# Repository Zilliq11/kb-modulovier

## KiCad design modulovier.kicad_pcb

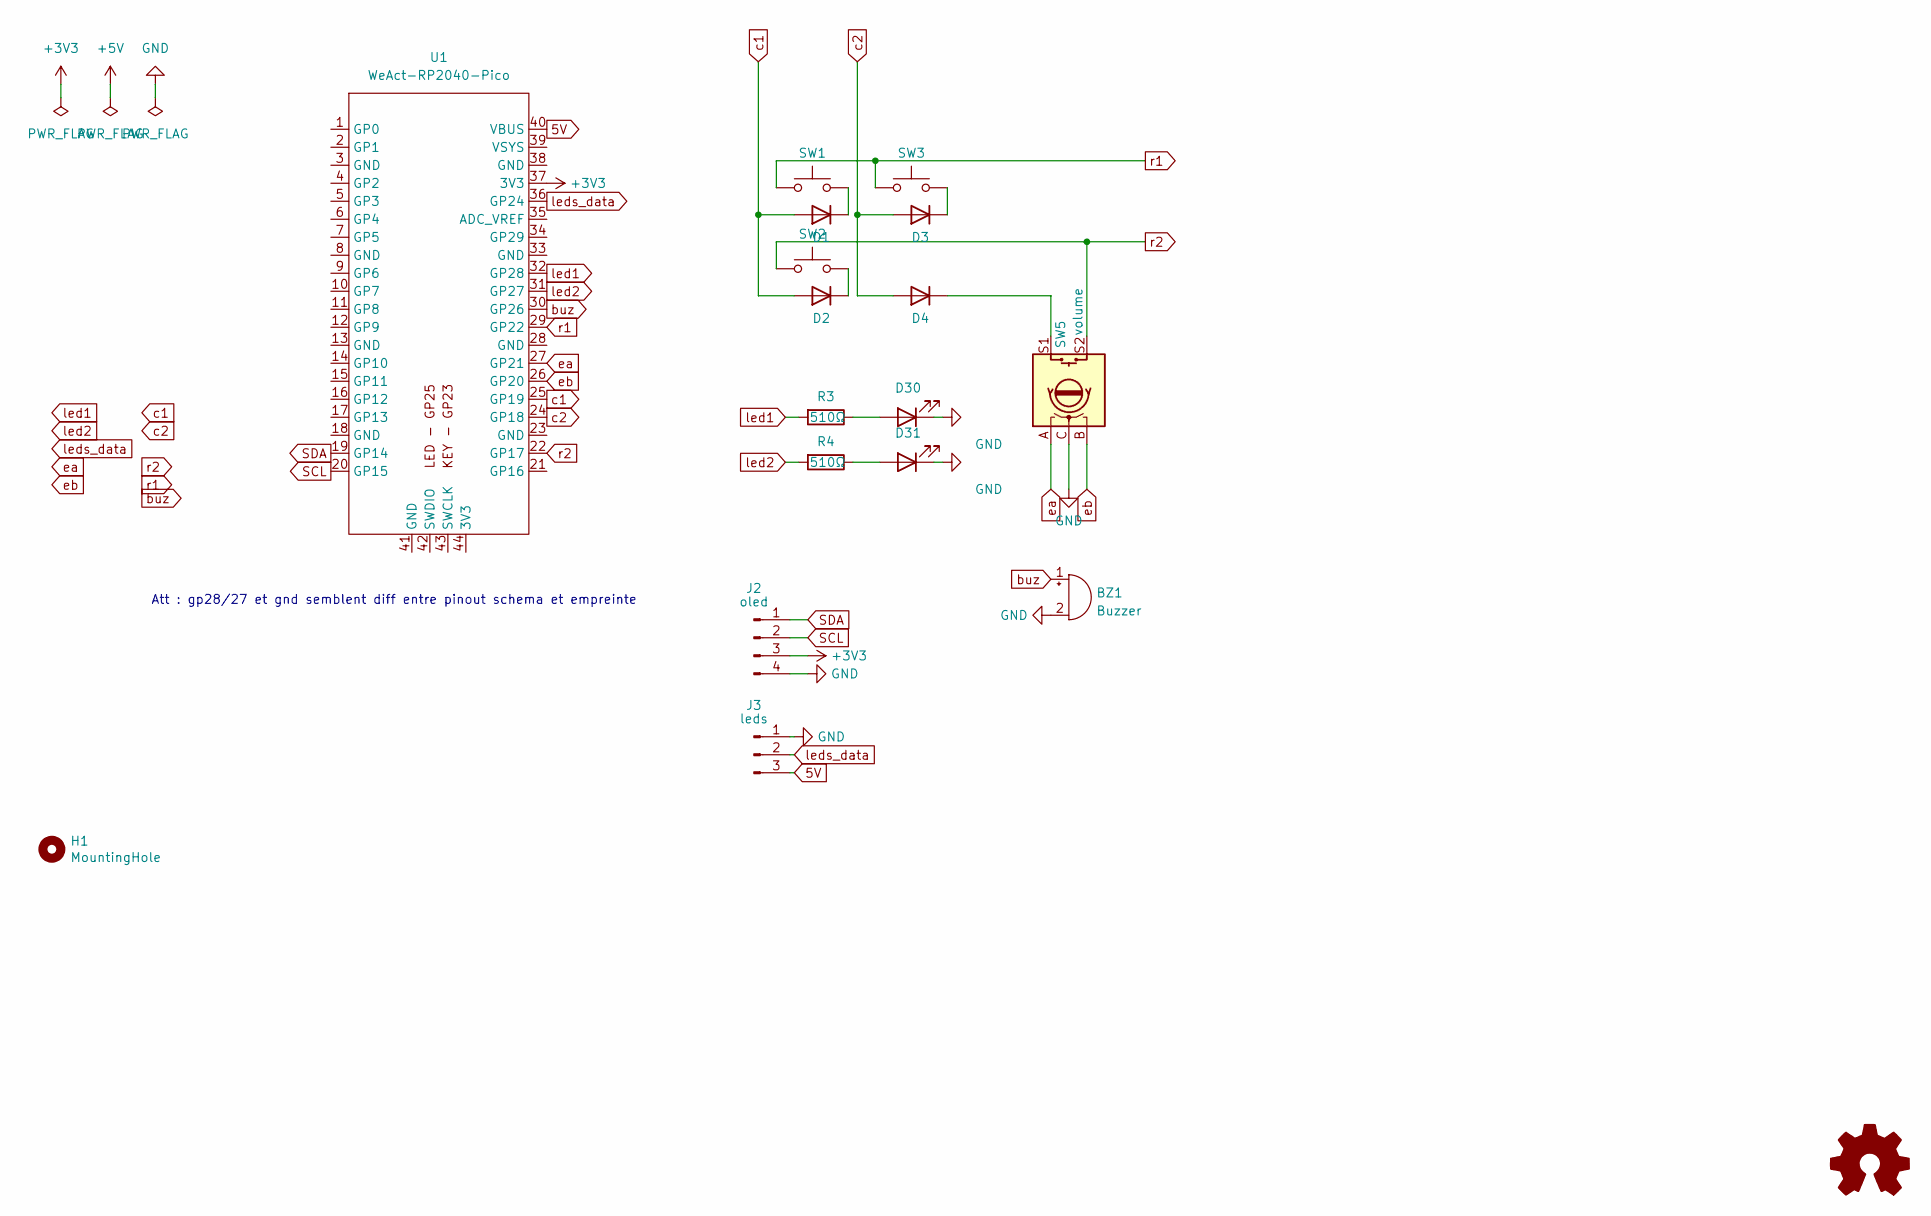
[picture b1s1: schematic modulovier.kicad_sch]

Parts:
BZ1: Buzzer; Buzzer_12x9.5RM7.6
D1, D2, D3, D4: D; D_1206_3216Metric_Pad1.42x1.75mm_HandSolder
D30: LED; LED_D3.0mm_lwr
D31: LED; LED_D3.0mm_rse
H1: MountingHole; LegoHole_12x12u_4875
J2: oled; OLED_128x32
J3: leds; JST_EH_S3B-EH_1x03_P2.50mm_Horizontal
R3, R4: 510Ω; R_1206_3216Metric_Pad1.30x1.75mm_HandSolder
SW1, SW2, SW3: mx; SW_Cherry_MX_1.00u_PCB
SW5: volume; RotaryEncoder_Alps_EC11E_Vertical_H20mm
U1: WeAct-RP2040-Pico

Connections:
5V: J3.3, U1.40 (VBUS)
+3V3: J2.3, U1.37 (3V3)
GND: BZ1.2 (+), D30.1 (K), D31.1 (K), J2.4, J3.1, SW5.C
unnamed: D1.1 (K), SW1.2
unnamed: D2.1 (K), SW2.2
unnamed: D3.1 (K), SW3.2
unnamed: D4.1 (K), SW5.S1
unnamed: D30.2 (A), R3.1
unnamed: D31.2 (A), R4.1
SCL: J2.2, U1.20 (GP15)
SDA: J2.1, U1.19 (GP14)
buz: BZ1.1 (-), U1.30 (GP26)
c1: D1.2 (A), D2.2 (A), U1.25 (GP19)
c2: D3.2 (A), D4.2 (A), U1.24 (GP18)
ea: SW5.A, U1.27 (GP21)
eb: SW5.B, U1.26 (GP20)
led1: R3.2, U1.32 (GP28)
led2: R4.2, U1.31 (GP27)
leds_data: J3.2, U1.36 (GP24)
r1: SW1.1, SW3.1, U1.29 (GP22)
r2: SW2.1, SW5.S2, U1.22 (GP17)

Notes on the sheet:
Att : gp28/27 et gnd semblent diff entre pinout schema et empreinte

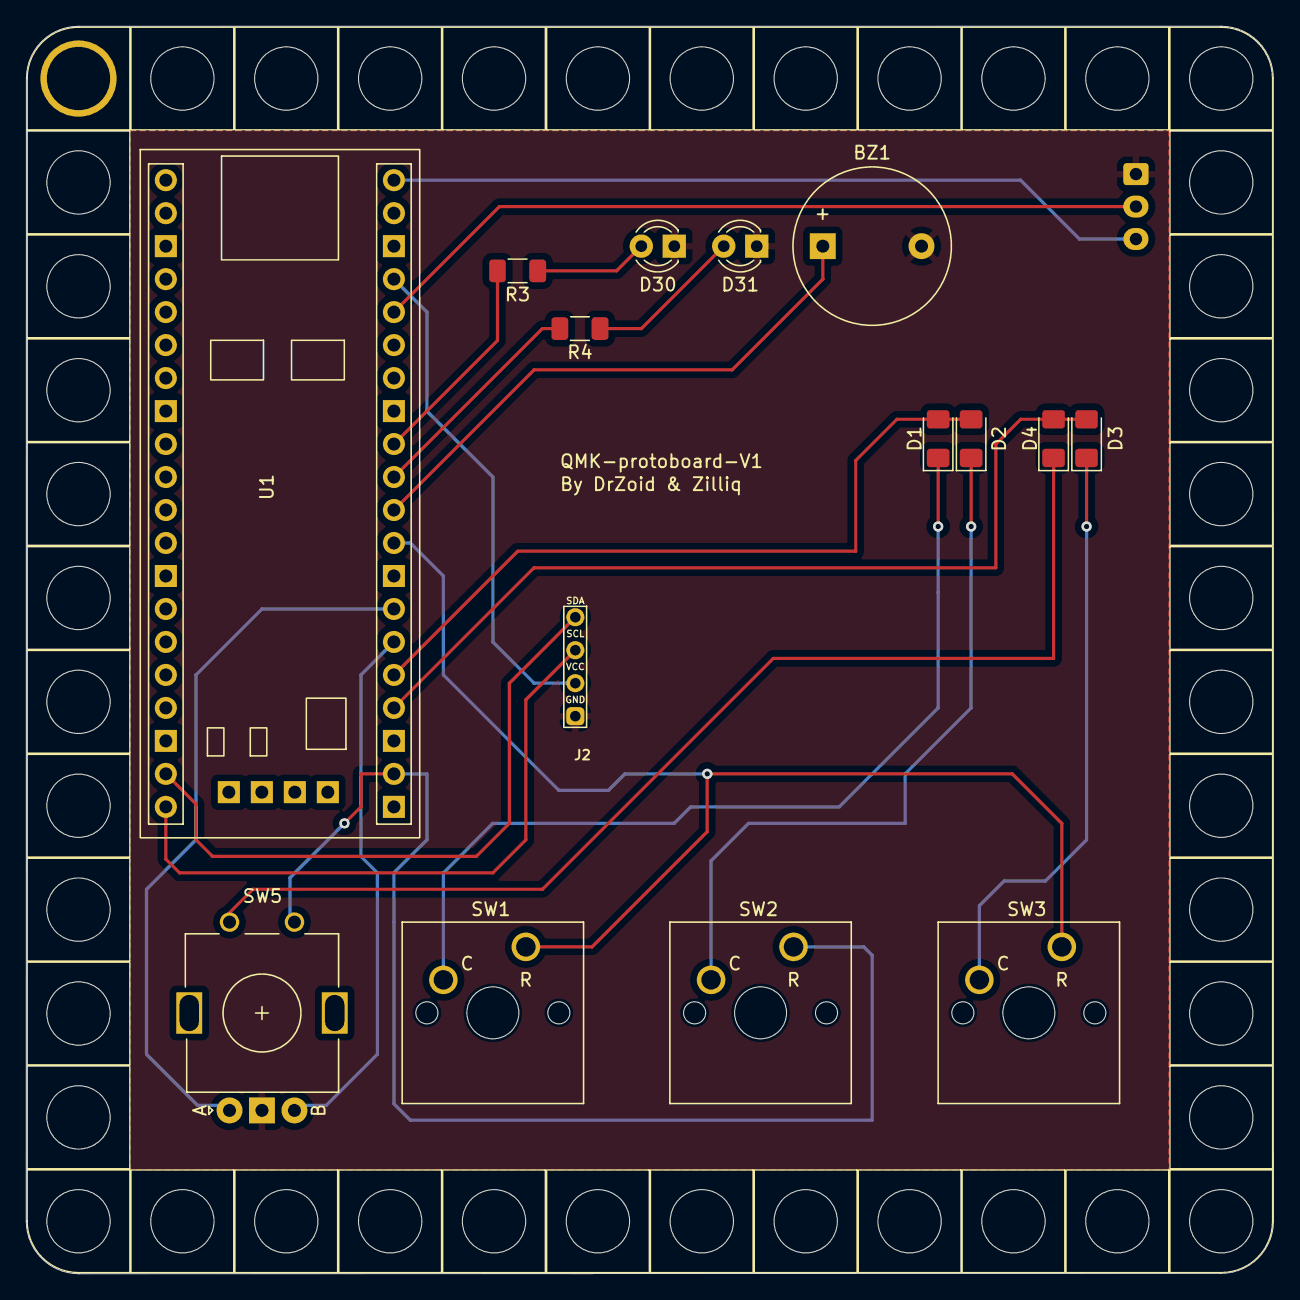
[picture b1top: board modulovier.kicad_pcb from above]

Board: 2 copper layers, 96.0 x 96.1 mm, 17 parts (1 on the bottom side), 21 nets.

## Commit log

2023-02-06 update schema
2023-03-12 Finished work to verify
